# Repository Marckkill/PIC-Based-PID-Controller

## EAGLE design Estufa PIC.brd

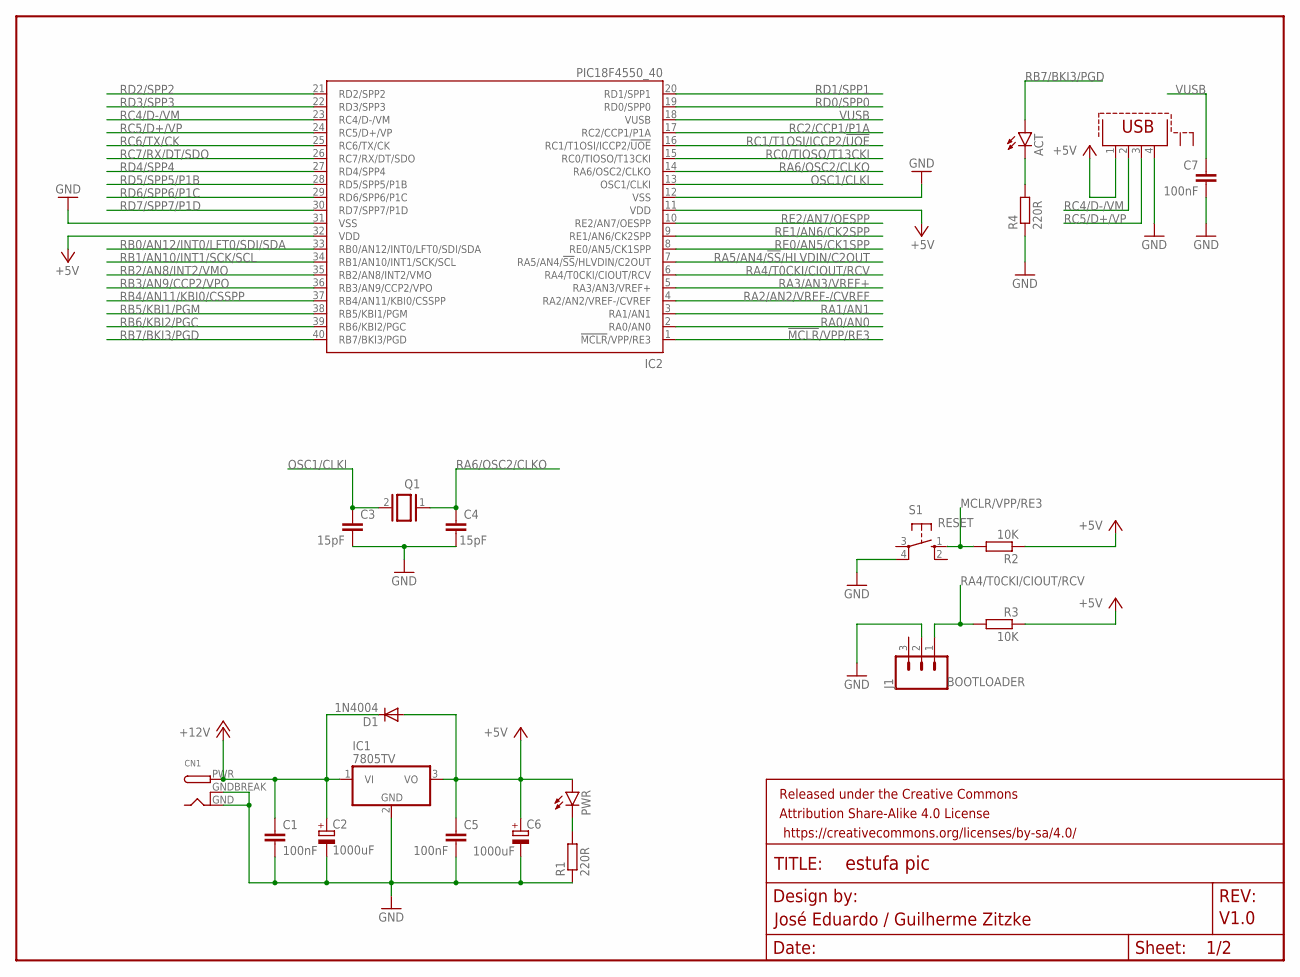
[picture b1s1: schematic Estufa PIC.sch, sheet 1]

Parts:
ACT: LED5MM
C1, C5, C7: 100nF; C025-025X050
C2, C6: 1000uF; E5-10,5
C3, C4: 15pF; C025-025X050
CN1: DCBARRELPTH; DCJACK_2MM_PTH
D1: 1N4004; DO41-10
FRAME1: FRAME-LETTERNO_PACKAGE; DUMMY
IC1: 7805TV; TO220V
IC2: PIC18F4550_40; DIL40
J1: BOOTLOADER; 1X03_LOCK
PWR: LED5MM
Q1: XTAL/S; QS
R1, R4: 220R; 0207/10
R2, R3: 10K; 0207/10
S1: RESET; B3F-40XX
X1: PN61729-S

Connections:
!MCLR!/VPP/RE3: IC2.1 (!MCLR!/VPP/RE3)
+5V: C5.1, C6.+, D1.A, IC1.3 (VO), IC2.11 (VDD), IC2.32 (VDD), PWR.A, R2.1, R3.1, X1.1; also elsewhere on the board
+12V: C1.1, C2.+, CN1.PWR, D1.C, IC1.1 (VI); also elsewhere on the board
GND: C1.2, C2.-, C3.2, C4.2, C5.2, C6.-, C7.2, CN1.GND, CN1.GNDBREAK, IC1.2 (GND), IC2.12 (VSS), IC2.31 (VSS), J1.2, R1.1, R4.1, S1.4 (P1), X1.4; also elsewhere on the board
MCLR/VPP/RE3: R2.2, S1.1 (S)
unnamed: ACT.K (C), R4.2
unnamed: PWR.K (C), R1.2
OSC1/CLKI: C3.1, IC2.13 (OSC1/CLKI), Q1.2
RA0/AN0: IC2.2 (RA0/AN0); also elsewhere on the board
RA1/AN1: IC2.3 (RA1/AN1)
RA2/AN2/VREF-/CVREF: IC2.4 (RA2/AN2/VREF-/CVREF)
RA3/AN3/VREF+: IC2.5 (RA3/AN3/VREF+)
RA4/T0CKI/CIOUT/RCV: IC2.6 (RA4/T0CKI/CIOUT/RCV), J1.1, R3.2
RA5/AN4/!SS!/HLVDIN/C2OUT: IC2.7 (RA5/AN4/!SS!/HLVDIN/C2OUT)
RA6/OSC2/CLKO: C4.1, IC2.14 (RA6/OSC2/CLKO), Q1.1
RB0/AN12/INT0/LFT0/SDI/SDA: IC2.33 (RB0/AN12/INT0/LFT0/SDI/SDA); also elsewhere on the board
RB1/AN10/INT1/SCK/SCL: IC2.34 (RB1/AN10/INT1/SCK/SCL); also elsewhere on the board
RB2/AN8/INT2/VMO: IC2.35 (RB2/AN8/INT2/VMO); also elsewhere on the board
RB3/AN9/CCP2/VPO: IC2.36 (RB3/AN9/CCP2/VPO); also elsewhere on the board
RB4/AN11/KBI0/CSSPP: IC2.37 (RB4/AN11/KBI0/CSSPP); also elsewhere on the board
RB5/KBI1/PGM: IC2.38 (RB5/KBI1/PGM); also elsewhere on the board
RB6/KBI2/PGC: IC2.39 (RB6/KBI2/PGC); also elsewhere on the board
RB7/BKI3/PGD: ACT.A, IC2.40 (RB7/BKI3/PGD)
RC0/TIOSO/T13CKI: IC2.15 (RC0/TIOSO/T13CKI)
RC1/T1OSI/ICCP2/!UOE: IC2.16 (RC1/T1OSI/ICCP2/!UOE); also elsewhere on the board
RC2/CCP1/P1A: IC2.17 (RC2/CCP1/P1A); also elsewhere on the board
RC4/D-/VM: IC2.23 (RC4/D-/VM), X1.2
RC5/D+/VP: IC2.24 (RC5/D+/VP), X1.3
RC6/TX/CK: IC2.25 (RC6/TX/CK)
RC7/RX/DT/SDO: IC2.26 (RC7/RX/DT/SDO)
RD0/SPP0: IC2.19 (RD0/SPP0)
RD1/SPP1: IC2.20 (RD1/SPP1)
RD2/SPP2: IC2.21 (RD2/SPP2)
RD3/SPP3: IC2.22 (RD3/SPP3)
RD4/SPP4: IC2.27 (RD4/SPP4)
RD5/SPP5/P1B: IC2.28 (RD5/SPP5/P1B)
RD6/SPP6/P1C: IC2.29 (RD6/SPP6/P1C)
RD7/SPP7/P1D: IC2.30 (RD7/SPP7/P1D)
RE0/AN5/CK1SPP: IC2.8 (RE0/AN5/CK1SPP)
RE1/AN6/CK2SPP: IC2.9 (RE1/AN6/CK2SPP)
RE2/AN7/OESPP: IC2.10 (RE2/AN7/OESPP)
VUSB: C7.1, IC2.18 (VUSB)

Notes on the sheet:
José Eduardo / Guilherme Zitzke
V1.0

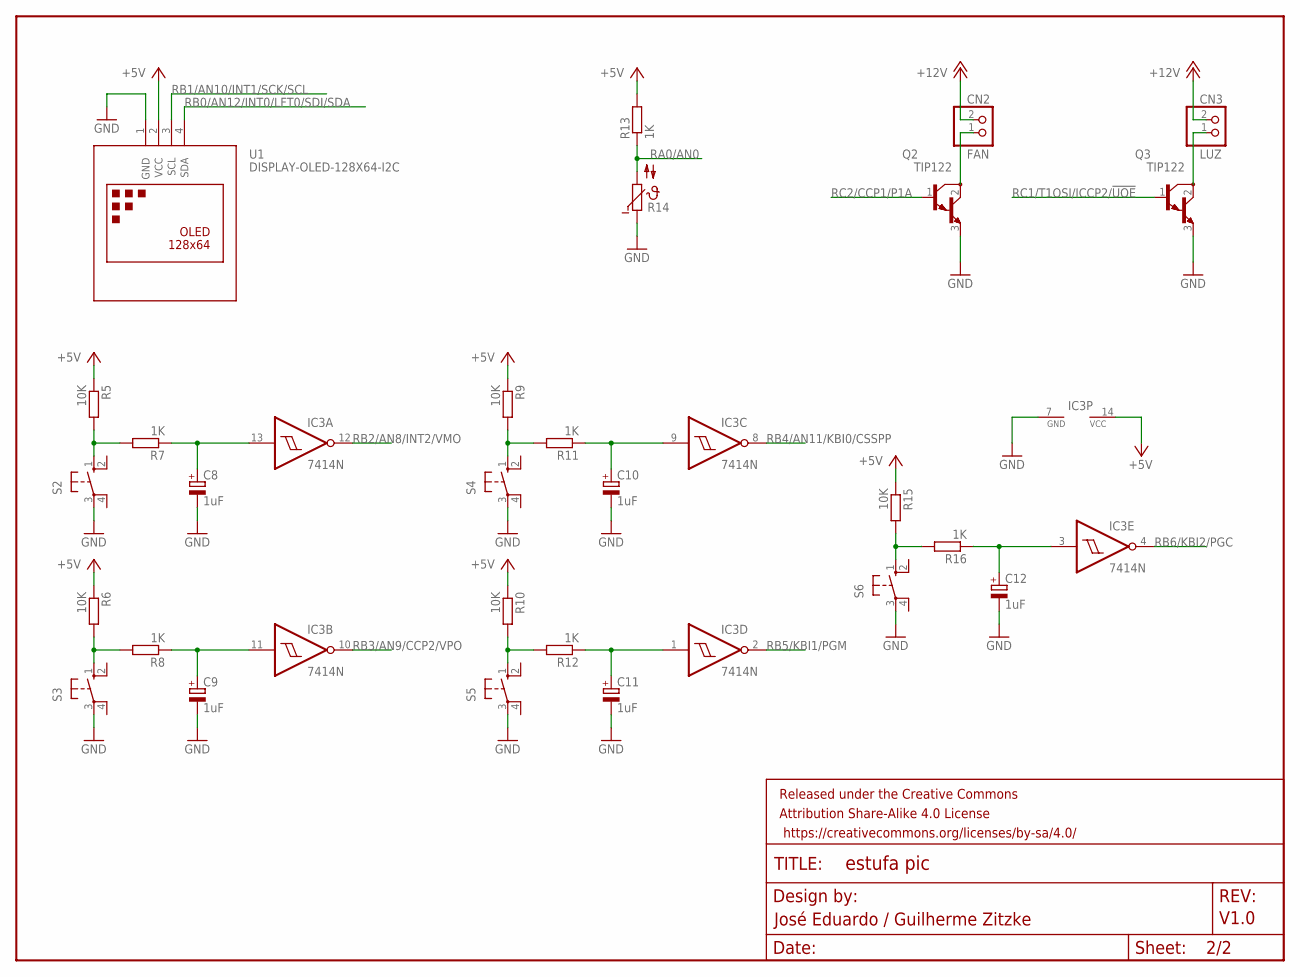
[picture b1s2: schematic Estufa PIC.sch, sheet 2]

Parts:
C8, C9, C10, C11, C12: 1uF; E2-5
CN2: FAN; JST-PH-2-THM
CN3: LUZ; JST-PH-2-THM
FRAME2: FRAME-LETTERNO_PACKAGE; DUMMY
IC3: 7414N; DIL14
Q2, Q3: TIP122; TO220V
R5, R6, R9, R10, R15: 10K; 0207/10
R7, R8, R11, R12, R13, R16: 1K; 0207/10
R14: NTC644C; N644C
S2, S3, S4, S5, S6: 40-XX; B3F-40XX
U1: DISPLAY-OLED-128X64-I2C

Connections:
+5V: IC3.14 (VCC), R5.1, R6.1, R9.1, R10.1, R13.2, R15.1, U1.2 (VCC); also elsewhere on the board
+12V: CN2.2 (1), CN3.2 (1); also elsewhere on the board
GND: C8.-, C9.-, C10.-, C11.-, C12.-, IC3.7 (GND), Q2.3 (E), Q3.3 (E), R14.1, S2.3, S3.3, S4.3, S5.3, S6.3, U1.1 (GND); also elsewhere on the board
unnamed: CN3.1 (2), Q3.2 (C)
unnamed: C8.+, IC3.13 (I), R7.1
unnamed: CN2.1 (2), Q2.2 (C)
unnamed: R6.2, R8.2, S3.1 (S)
unnamed: C9.+, IC3.11 (I), R8.1
unnamed: R9.2, R11.2, S4.1 (S)
unnamed: C10.+, IC3.9 (I), R11.1
unnamed: R5.2, R7.2, S2.1 (S)
unnamed: R10.2, R12.2, S5.1 (S)
unnamed: C11.+, IC3.1 (I), R12.1
unnamed: R15.2, R16.2, S6.1 (S)
unnamed: C12.+, IC3.3 (I), R16.1
RA0/AN0: R13.1, R14.2; also elsewhere on the board
RB0/AN12/INT0/LFT0/SDI/SDA: U1.4 (SDA); also elsewhere on the board
RB1/AN10/INT1/SCK/SCL: U1.3 (SCL); also elsewhere on the board
RB2/AN8/INT2/VMO: IC3.12 (O); also elsewhere on the board
RB3/AN9/CCP2/VPO: IC3.10 (O); also elsewhere on the board
RB4/AN11/KBI0/CSSPP: IC3.8 (O); also elsewhere on the board
RB5/KBI1/PGM: IC3.2 (O); also elsewhere on the board
RB6/KBI2/PGC: IC3.4 (O); also elsewhere on the board
RC1/T1OSI/ICCP2/!UOE: Q3.1 (B); also elsewhere on the board
RC2/CCP1/P1A: Q2.1 (B); also elsewhere on the board

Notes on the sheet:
José Eduardo / Guilherme Zitzke
V1.0

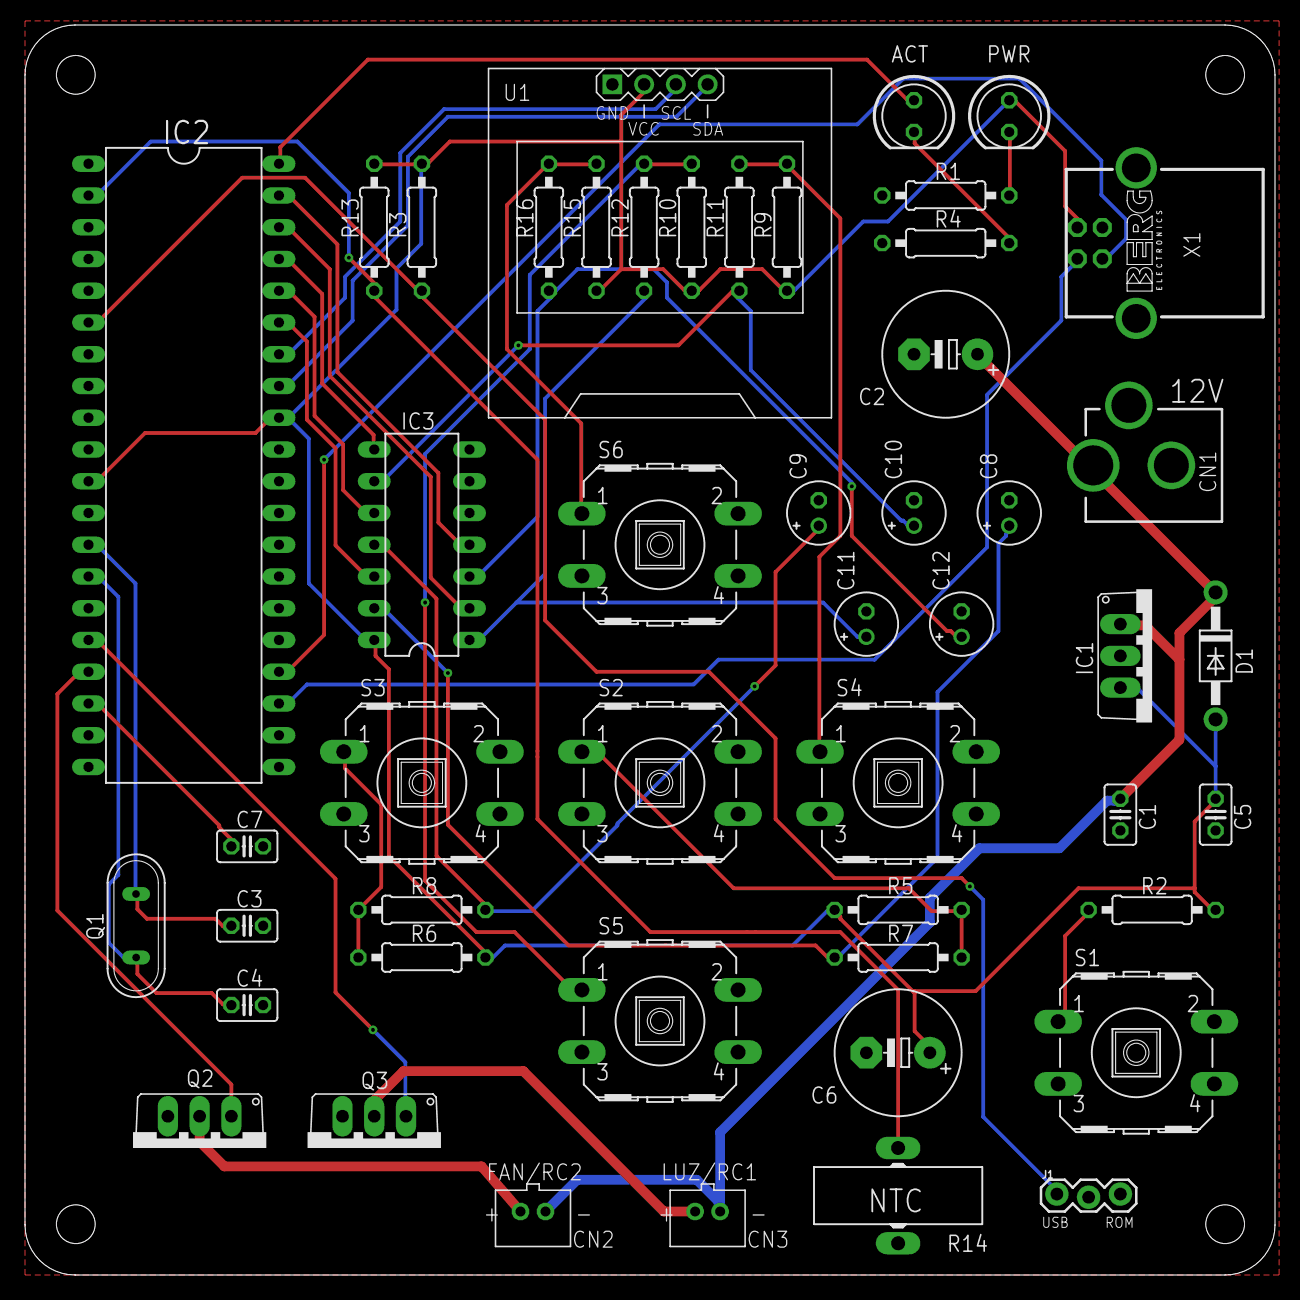
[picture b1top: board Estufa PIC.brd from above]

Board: 2 copper layers, 100.0 x 100.0 mm, 51 parts (0 on the bottom side), 35 nets.

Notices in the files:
parts and their libraries:
SparkFun-Aesthetics: Licensing: Creative Commons ShareAlike 4.0 International - https://creativecommons.org/licenses/by-sa/4.0
diy-modules: Released under the Creative Commons Attribution 4.0 International License: http://creativecommons.org/licenses/by/4.0
